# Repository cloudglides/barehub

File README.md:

<h1 align="center">BAREHUB</h1>

<p align="center">
  <a href="https://www.youtube.com/watch?v=AxE4TltnvjI">BUILD!(not yet) • </a>
 <a href="https://cad.onshape.com/documents/4b9bd96242774528e3dbc81e/w/aa711833ecff2e684d7276d3/e/eb8acac42691808165e34fed">Onshape timeline</a>
</p>

<p align="center">
   A very very cool minimal USB hub featuring 1 USB-C in, 4 USB-A out, small PCB, fast USB 2.0.
</p>

<details>
<summary><strong>3D Case</strong></summary>

<br>

</details>

<br>

<details>
<summary><strong>PCB / Schematic</strong></summary>

<br>

<br>

</details>

<br>

<details>
<summary><strong>Build Instructions</strong></summary>

<br>

<p>
  To assemble the BAREHUB PCB:
</p>

<ol>
  <li>Apply solder paste to the pads of the PCB.</li>
  <li>Place all components (FE1.1S IC, USB ports, capacitors, etc.) onto their pads.</li>
  <li>Use a hotplate(reccomended) or hot-air gun to reflow the solder paste and solder components down.</li>
  <li>Inspect solder joints and touch up any misaligned components(dont burn em duh) if needed.</li>
</ol>

</details>

<br>

<details>
<summary><strong>License</strong></summary>

<br>

<p>
This project is licensed under a <b>Creative Commons Attribution-NonCommercial-ShareAlike style license with commercial permission</b>:
</p>

<ul>
  <li>You are free to copy, modify, and sell products based on this design.</li>
  <li>You <b>must credit "BAREHUB by cloudglides"</b> wherever the design is used.</li>
  <li>Derivatives are allowed and can be sold, but attribution is required.</li>
</ul>

<p>
In short: <b>copy, earn, remix, but always credit the original creator.</b>
</p>

</details>

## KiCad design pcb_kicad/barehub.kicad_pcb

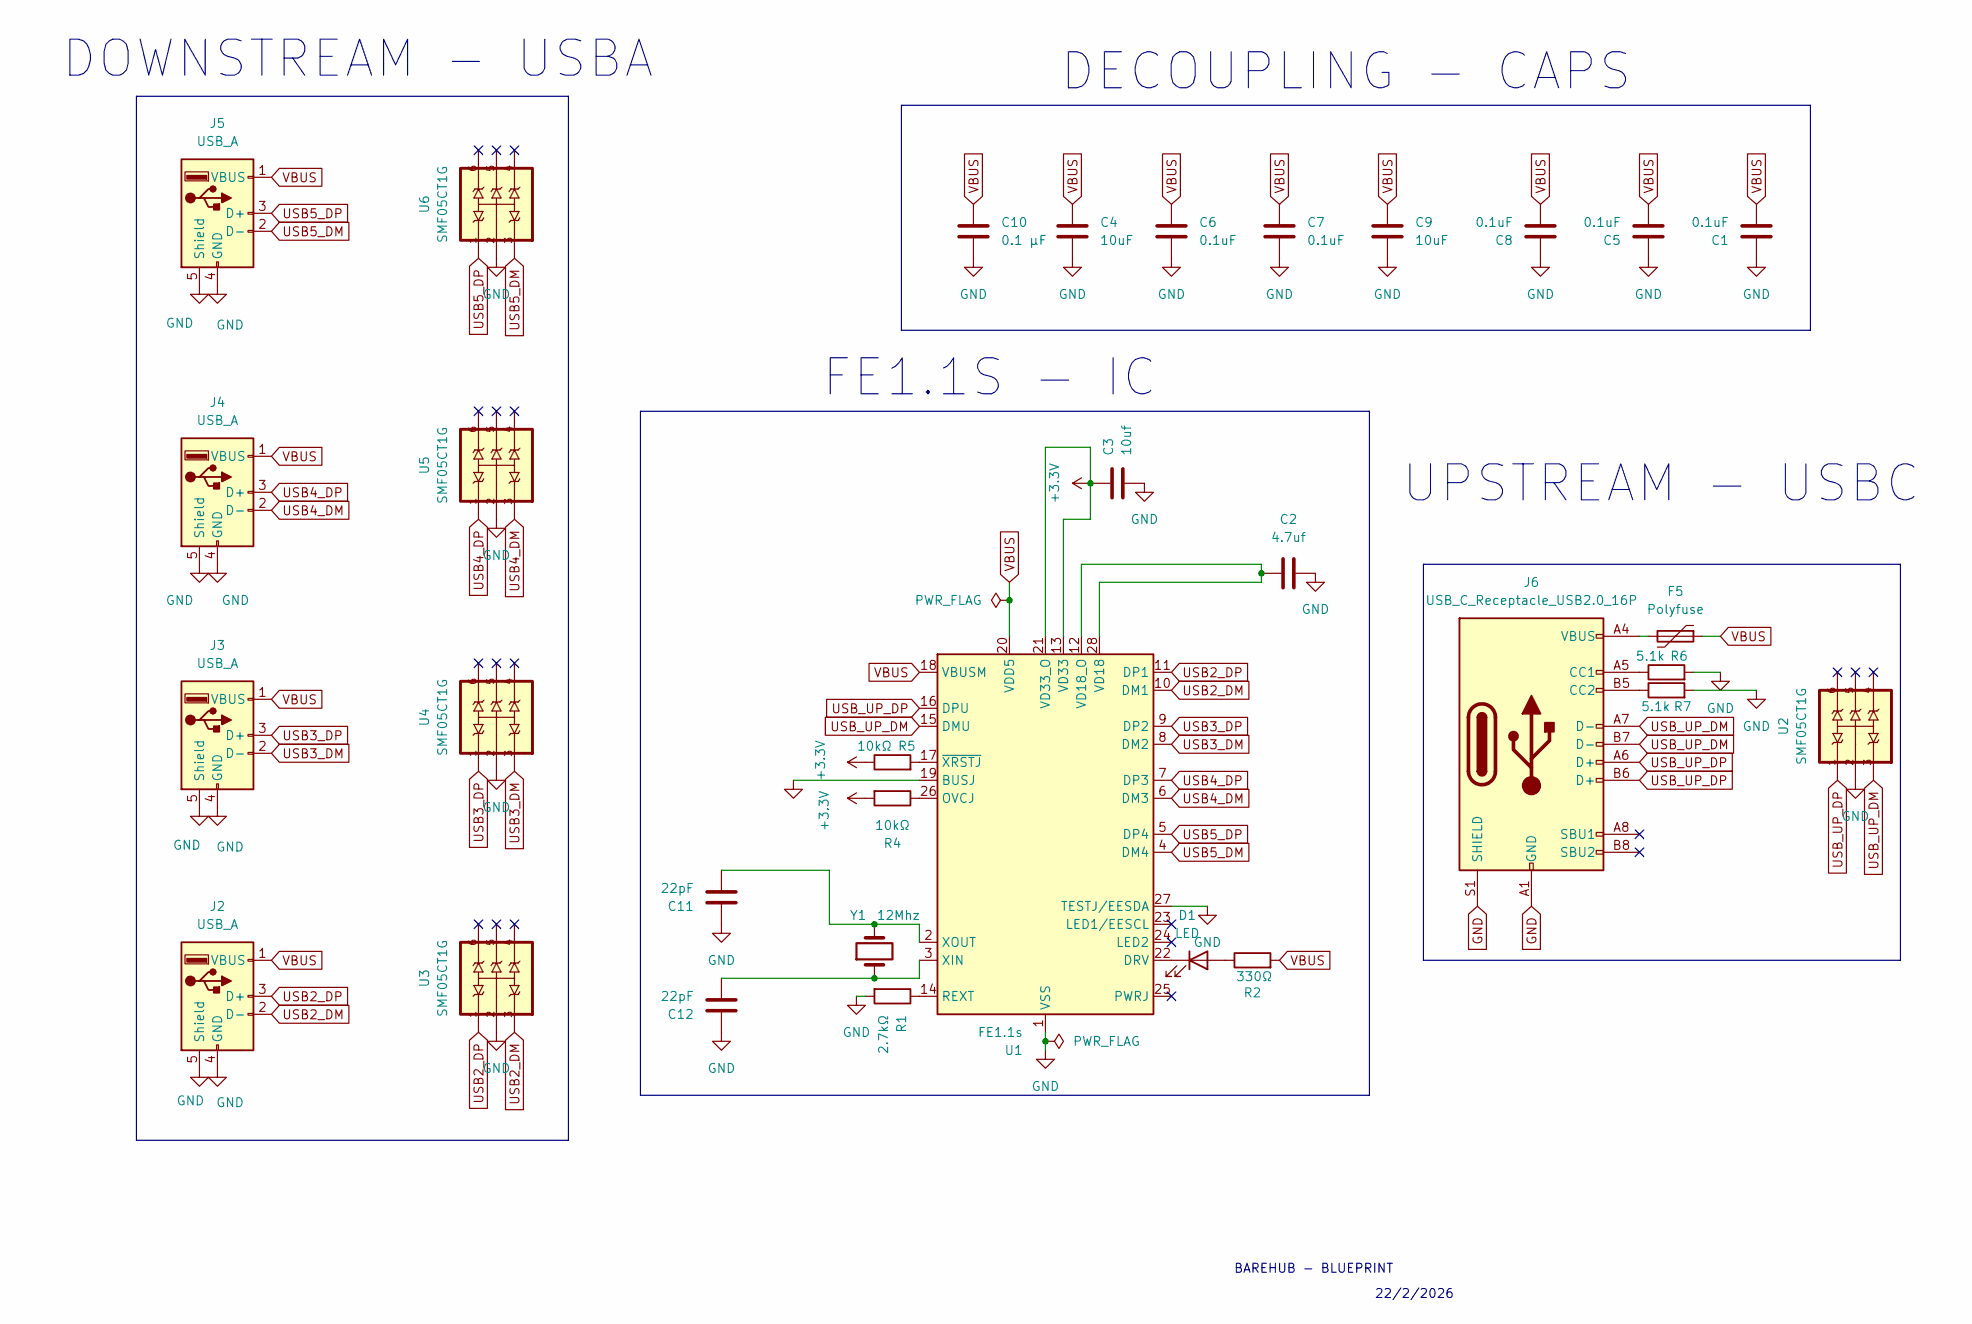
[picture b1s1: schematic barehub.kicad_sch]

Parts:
C1, C5, C6, C7, C8: 0.1uF; C_0603_1608Metric
C2: 4.7uf; C_0805_2012Metric
C3: 10uf; C_0805_2012Metric
C4: 10uF; C_0805_2012Metric
C9: 10uF; C_0603_1608Metric
C10: 0.1 µF; C_0603_1608Metric
C11, C12: 22pF; C_1206_3216Metric
D1: LED; LED_1206_3216Metric
F5: Polyfuse; Fuse_1206_3216Metric
J2, J3, J4, J5: USB_A; USB_A_Molex_105057_Vertical
J6: USB_C_Receptacle_USB2.0_16P; USB_C_Receptacle_HRO_TYPE-C-31-M-12
R1: 2.7kΩ; R_0603_1608Metric
R2: 330Ω; R_0603_1608Metric
R4, R5: 10kΩ; R_0603_1608Metric
R6, R7: 5.1k; R_0603_1608Metric
U1: FE1.1s; SSOP-28_3.9x9.9mm_P0.635mm
U2, U3, U4, U5, U6: SMF05CT1G; SOT65P210X110-6N
Y1: 12Mhz; Crystal_SMD_3225-4Pin_3.2x2.5mm

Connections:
+3.3V: C3.2, R4.2, R5.1, U1.13 (VD33), U1.21 (VD33_O)
GND: C1.1, C2.2, C3.1, C4.2, C5.1, C6.2, C7.2, C8.1, C9.2, C10.2, C11.1, C12.1, J2.4 (GND), J2.5 (Shield), J3.4 (GND), J3.5 (Shield), J4.4 (GND), J4.5 (Shield), J5.4 (GND), J5.5 (Shield), J6.A1 (GND), J6.A12 (GND), J6.B1 (GND), J6.B12 (GND), J6.S1 (SHIELD), R1.2, R6.2, R7.2, U1.1 (VSS), U1.19 (BUSJ), U1.27 (TESTJ/EESDA), U2.2, U3.2, U4.2, U5.2, U6.2
unnamed: D1.2 (A), R2.1
unnamed: D1.1 (K), U1.22 (DRV)
unnamed: F5.2, J6.A4 (VBUS), J6.A9 (VBUS), J6.B4 (VBUS), J6.B9 (VBUS)
unnamed: J6.A5 (CC1), R6.1
unnamed: J6.B5 (CC2), R7.1
unnamed: R4.1, U1.26 (OVCJ)
unnamed: R1.1, U1.14 (REXT)
unnamed: C2.1, U1.12 (VD18_O), U1.28 (VD18)
unnamed: C12.2, U1.3 (XIN), Y1.1
unnamed: C11.2, U1.2 (XOUT), Y1.2
unnamed: R5.2, U1.17 (~XRSTJ)
USB2_DM: J2.2 (D-), U1.10 (DM1), U3.3
USB2_DP: J2.3 (D+), U1.11 (DP1), U3.1
USB3_DM: J3.2 (D-), U1.8 (DM2), U4.3
USB3_DP: J3.3 (D+), U1.9 (DP2), U4.1
USB4_DM: J4.2 (D-), U1.6 (DM3), U5.3
USB4_DP: J4.3 (D+), U1.7 (DP3), U5.1
USB5_DM: J5.2 (D-), U1.4 (DM4), U6.3
USB5_DP: J5.3 (D+), U1.5 (DP4), U6.1
USB_UP_DM: J6.A7 (D-), J6.B7 (D-), U1.15 (DMU), U2.3
USB_UP_DP: J6.A6 (D+), J6.B6 (D+), U1.16 (DPU), U2.1
VBUS: C1.2, C4.1, C5.2, C6.1, C7.1, C8.2, C9.1, C10.1, F5.1, J2.1 (VBUS), J3.1 (VBUS), J4.1 (VBUS), J5.1 (VBUS), R2.2, U1.18 (VBUSM), U1.20 (VDD5)

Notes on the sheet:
DECOUPLING - CAPS
FE1.1S - IC
UPSTREAM - USBC
22/2/2026
DOWNSTREAM - USBA
BAREHUB - BLUEPRINT

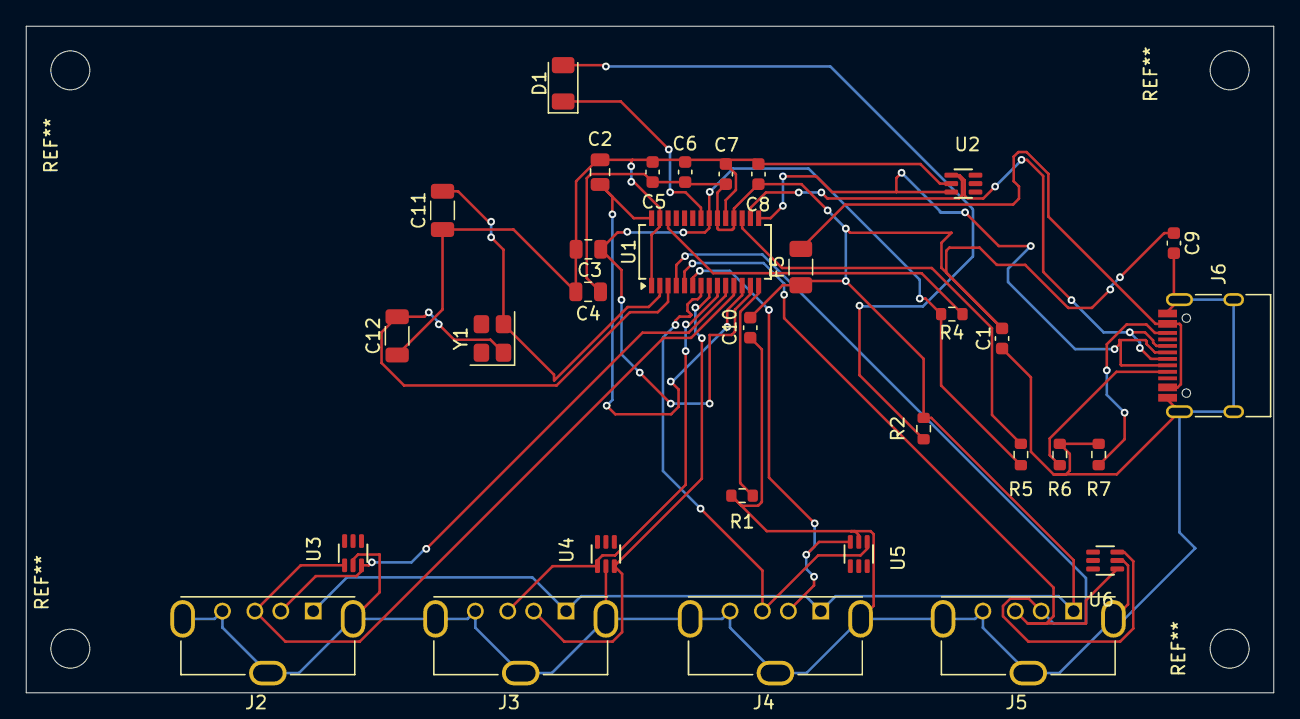
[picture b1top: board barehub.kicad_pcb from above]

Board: 2 copper layers, 96.2 x 51.4 mm, 32 parts (0 on the bottom side), 24 nets.

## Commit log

2026-02-22 init
2026-02-22 chore: add readme
2026-02-22 [ImgBot] Optimize images
    *Total -- 1,397.16kb -> 1,275.36kb (8.72%)
    /pcb_kicad/barehub.png -- 343.12kb -> 289.67kb (15.58%)
    /pcb_kicad/barehub.svg -- 1,054.04kb -> 985.68kb (6.48%)
2026-02-22 update: readme tweaks
2026-02-22 chore: add BOM
2026-02-22 chore: add BOM (opssie)
2026-02-22 update: onshape timeline link & readme tweaks
2026-02-22 fixes: format
2026-02-22 fixes: oopsies
2026-02-22 update: image in readme
2026-02-23 fixes: wrong link
